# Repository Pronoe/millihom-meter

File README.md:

# milliohm-meter
Portable and low cost milliommeter with good performances

# Introduction
When you have to debug electronic systems or find failure on an electronic board or electrical system, you frequently need to locate short circuits.
Common multimeters  are generally limited down to 1 ohm in their measurement and this is not sufficient for efficient characterization and localization of a short circuit.
Below the 1 ohm domain, a milliohmmemeter is the required instrument but Industrial miiliohmmeters are expensive so I decided to build my own device.

# General design
I had viewed a good publication for a DIY milliohmmeter from the "Electro-bidouilleur" YouTube channel. The Elektor magazine sells also a add-on device for multimeters.
However this projects suffers several drawbacks:
-	need a separate multimeter for the measurement
-	provides no protection against excessive voltage on the device under test
-	do not use 4 wires measurement for better accuracy
The main characteristics of my design are:
-	use of a INA199 from Texas Instrument for the measurement
o	this is a Voltage-Output, Current-Shunt Monitor which need no additional component
o	provides very low offset voltage and very low drift
o	high accuracy gain
-	current source of 10.6 mA build with a ½ TLC272 which is a precision dual operational amplifier
-	voltage limiter with a BC548 transistor
-	use of and Arduino Uno board for:
o	output voltage measurement,
o	resistance computation from voltage measurement
o	initial zero compensation
o	full range calibration
-	use of a 2 lines x 16 characters LCD display shield for user interface
-	use of a a 1200 mAh LiPo battery combined with a step up converter/ battery charger  for portable operation
-	use of a "Kelvin" 4 wires cable for device connection

see detailed information in technical files

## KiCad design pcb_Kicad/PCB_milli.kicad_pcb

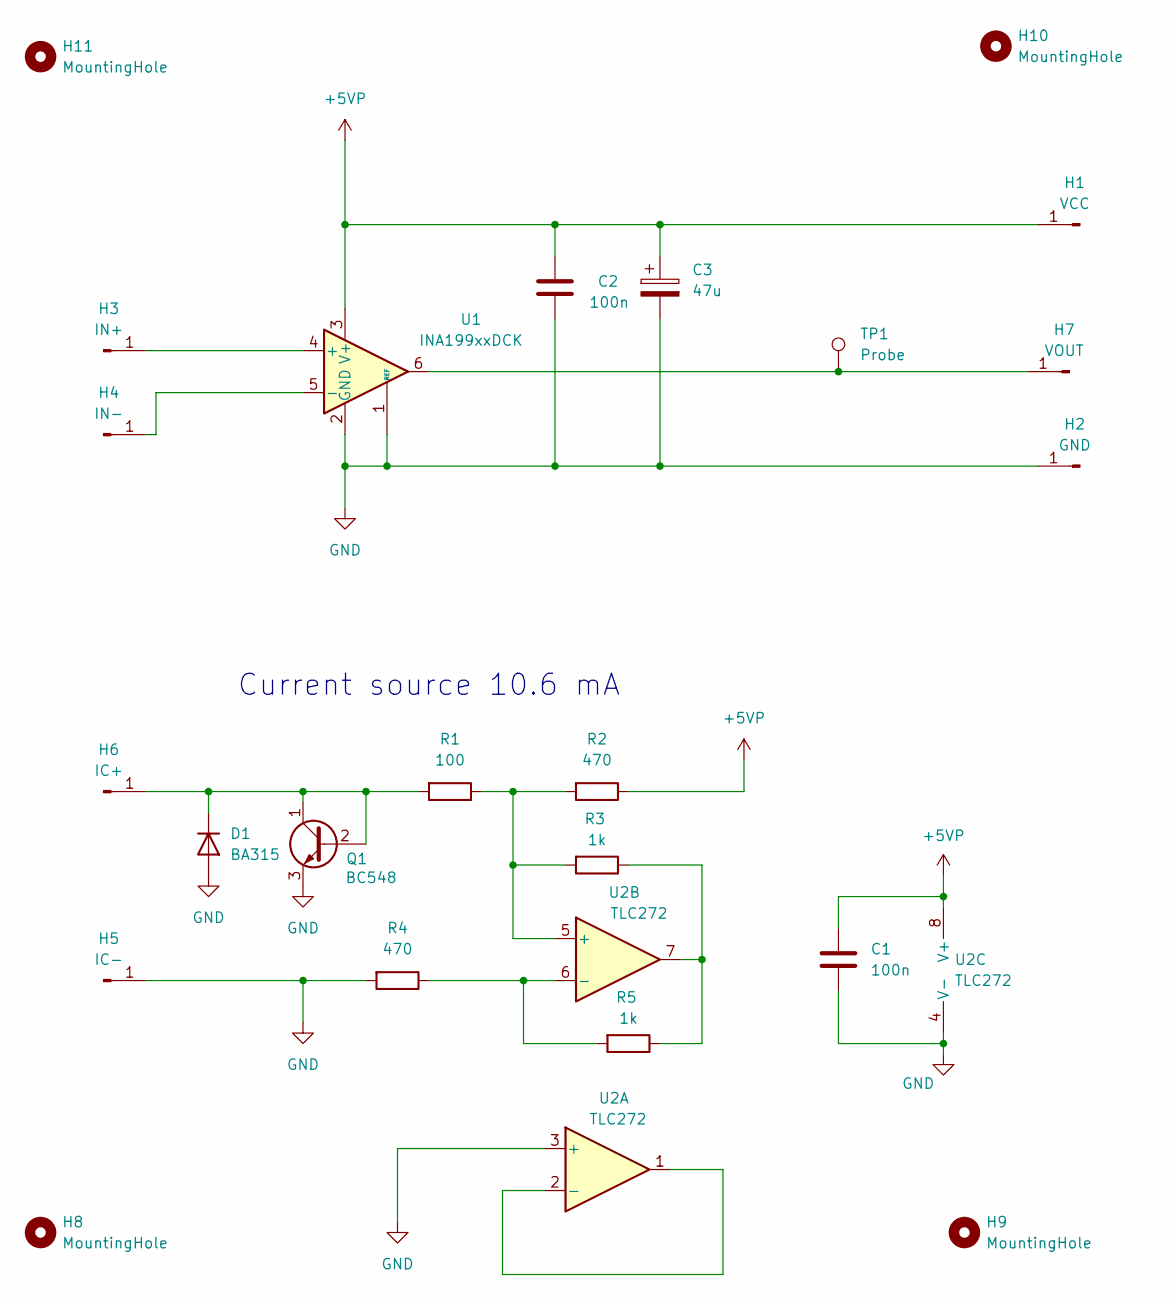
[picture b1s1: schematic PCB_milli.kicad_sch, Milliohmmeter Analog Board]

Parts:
C1, C2: 100n; C_Disc_D5.0mm_W2.5mm_P2.50mm
C3: 47u; CP_Axial_L11.0mm_D6.0mm_P18.00mm_Horizontal
D1: BA315; D_DO-35_SOD27_P7.62mm_Horizontal
H1: VCC; SolderWire-0.5sqmm_1x01_D0.9mm_OD2.1mm_Relief
H2: GND; SolderWire-0.5sqmm_1x01_D0.9mm_OD2.1mm_Relief
H3: IN+; SolderWire-0.5sqmm_1x01_D0.9mm_OD2.1mm_Relief
H4: IN-; SolderWire-0.5sqmm_1x01_D0.9mm_OD2.1mm_Relief
H5: IC-; SolderWire-0.5sqmm_1x01_D0.9mm_OD2.1mm_Relief
H6: IC+; SolderWire-0.5sqmm_1x01_D0.9mm_OD2.1mm_Relief
H7: VOUT; SolderWire-0.5sqmm_1x01_D0.9mm_OD2.1mm_Relief
H8, H9, H10, H11: MountingHole; MountingHole_3.2mm_M3
Q1: BC548; TO-92_Inline
R1: 100; R_Axial_DIN0207_L6.3mm_D2.5mm_P10.16mm_Horizontal
R2, R4: 470; R_Axial_DIN0207_L6.3mm_D2.5mm_P10.16mm_Horizontal
R3, R5: 1k; R_Axial_DIN0207_L6.3mm_D2.5mm_P10.16mm_Horizontal
TP1: Probe; TestPoint_THTPad_2.0x2.0mm_Drill1.0mm
U1: INA199xxDCK; SOT-363_SC-70-6
U2: TLC272; DIP-8_W7.62mm

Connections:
+5VP: C1.1, C2.1, C3.1, H1.1, R2.1, U1.3 (V+), U2.8 (V+)
GND: C1.2, C2.2, C3.2, D1.2 (A), H2.1, H5.1, Q1.3 (E), R4.2, U1.1 (REF), U1.2 (GND), U2.3 (+), U2.4 (V-)
unnamed: D1.1 (K), H6.1, Q1.1 (C), Q1.2 (B), R1.2
unnamed: H3.1, U1.4 (+)
unnamed: H4.1, U1.5 (-)
unnamed: H7.1, TP1.1, U1.6
unnamed: R3.1, R5.1, U2.7
unnamed: U2.1, U2.2 (-)
unnamed: R1.1, R2.2, R3.2, U2.5 (+)
unnamed: R4.1, R5.2, U2.6 (-)

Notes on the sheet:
Current source 10.6 mA

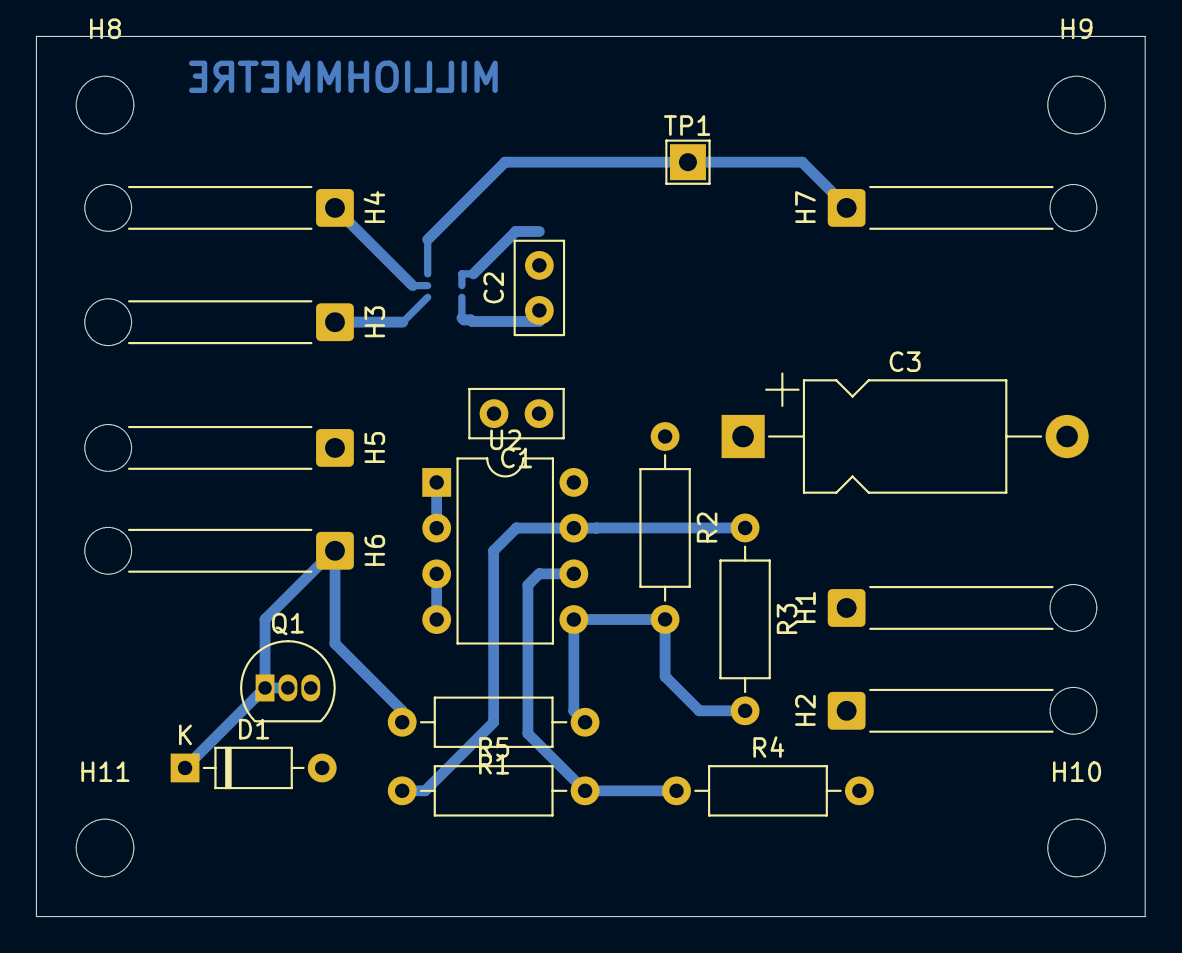
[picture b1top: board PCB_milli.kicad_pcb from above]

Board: 2 copper layers, 61.6 x 48.9 mm, 24 parts (1 on the bottom side), 10 nets.

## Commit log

2025-05-22 1st repo update
2025-05-22 Delete ~WRL0003.tmp
    unknown file
2025-05-22 Delete ~$scription.docx
    unknown temp file
